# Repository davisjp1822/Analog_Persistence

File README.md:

# Analog_Persistence
Educational board showing an industrial 4-20mA or 0-10V input using a MCP3424 A/D and AD8220 Diffamp

Purchase the complete board at the [ThreeML website](https://www.three-ml.com/product/analog-persistence/)

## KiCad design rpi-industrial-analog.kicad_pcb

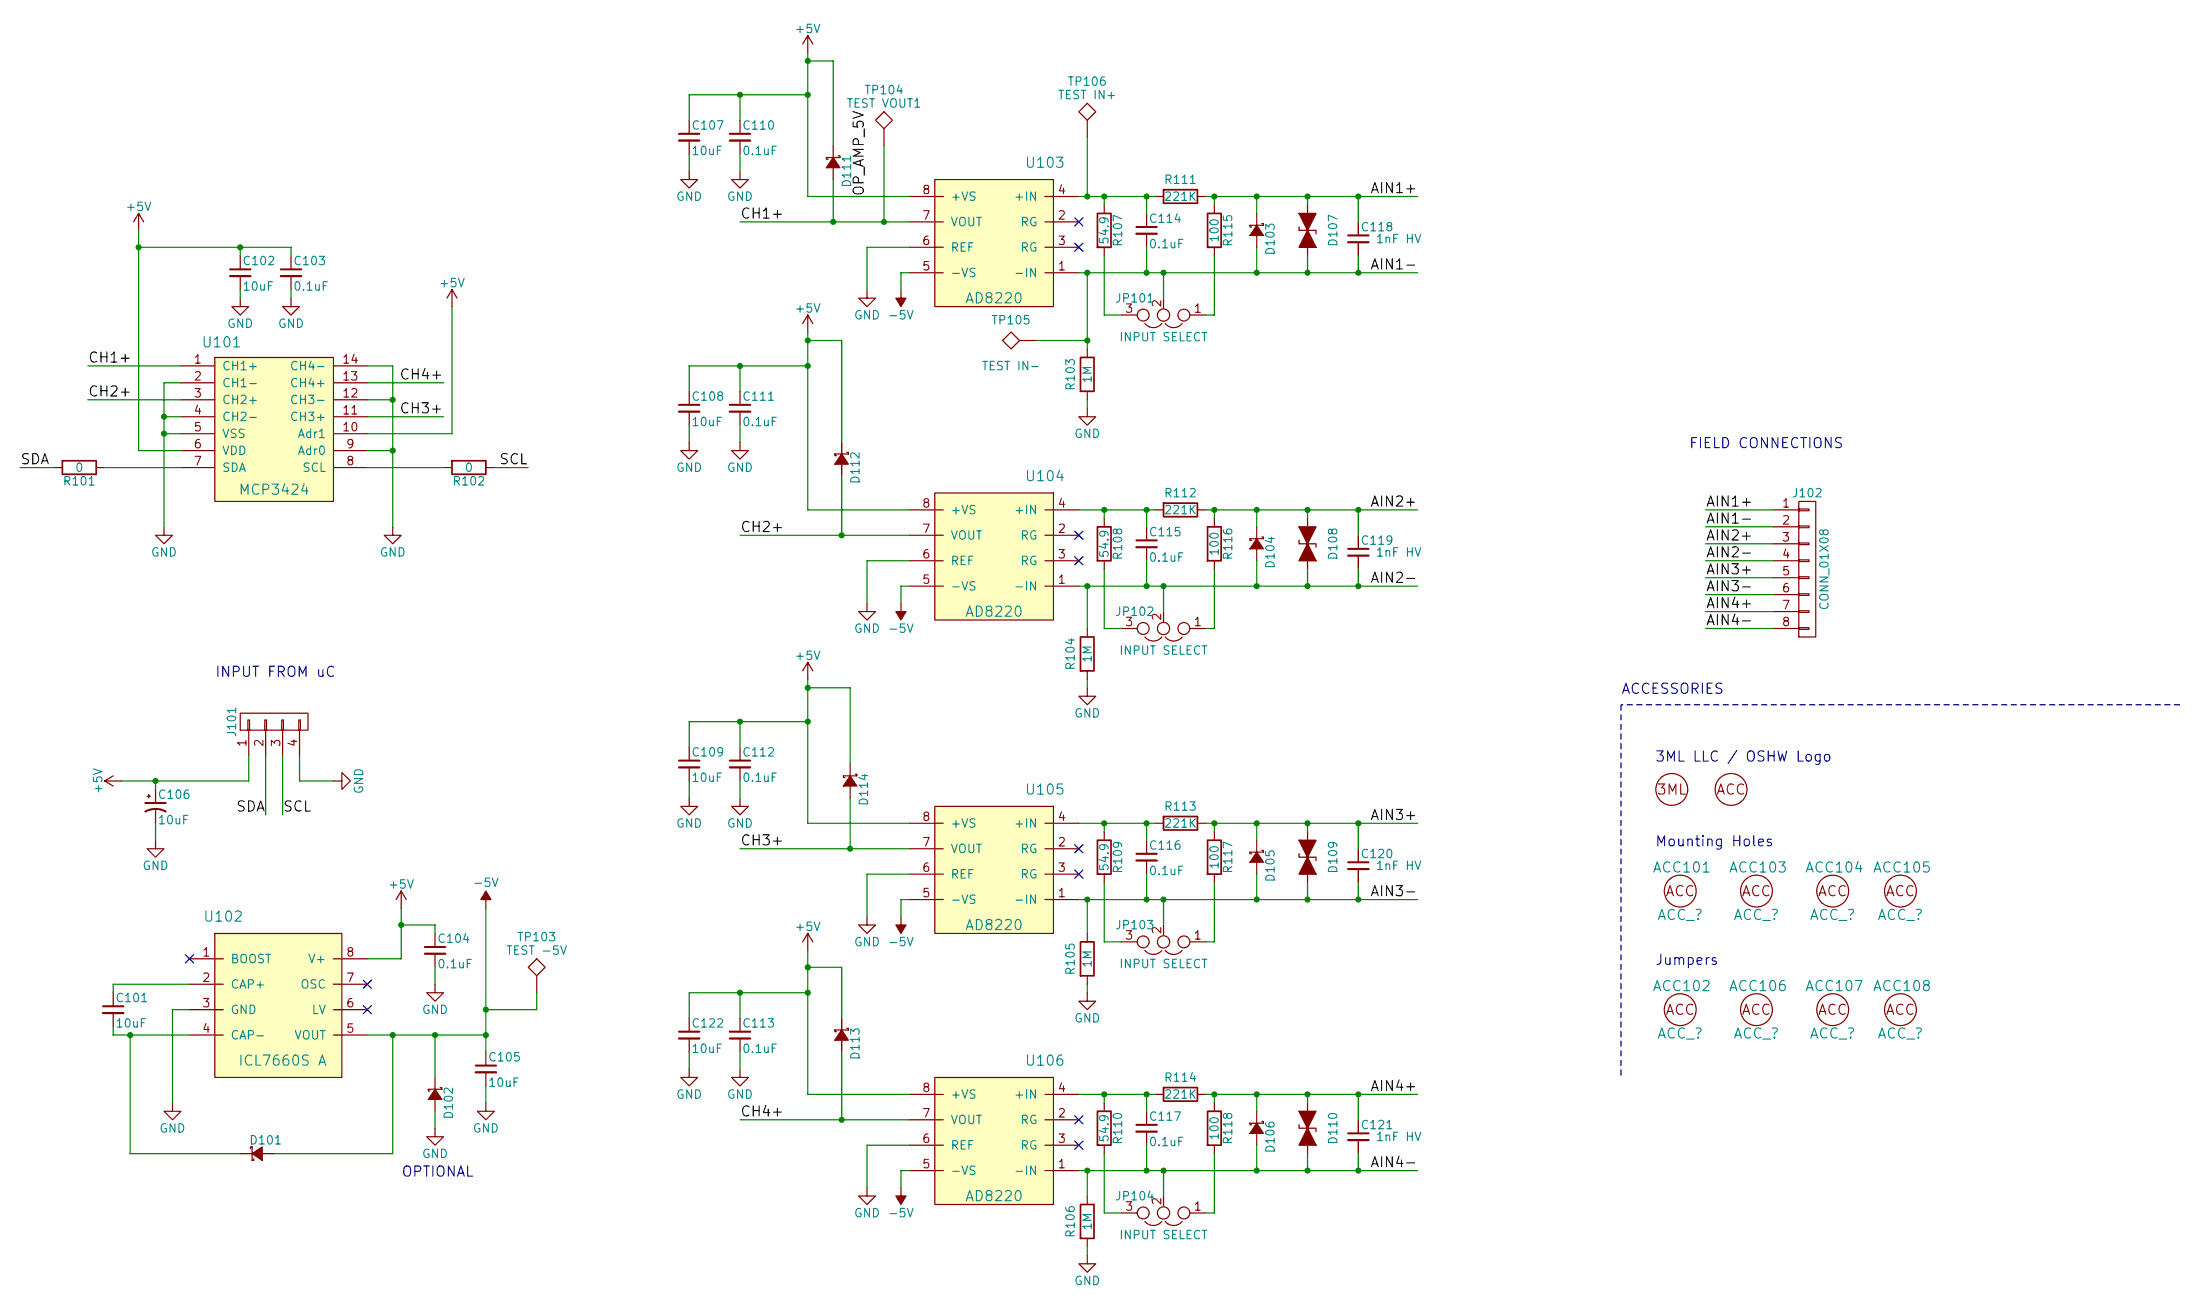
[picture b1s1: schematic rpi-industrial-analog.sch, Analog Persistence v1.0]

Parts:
ACC101, ACC103, ACC104, ACC105: ACC_?; MountingHole_3.2mm_M3_DIN965; MPN X
ACC102, ACC106, ACC107, ACC108: ACC_?; X; MPN NPB02SVAN-RC
ACC109: ACC_?; OSHW-Logo_11.4x12mm_SilkScreen
C101, C102, C105, C107, C108, C109, C122: 10uF; C_0805; MPN CL21B106KOQNNNG
C103, C104, C110, C111, C112, C113, C114, C115, C116, C117: 0.1uF; C_0805; MPN 08055C104KAT2A
C106: 10uF; CP_Tantalum_Case-A_EIA-3216-18_Reflow; MPN F931A106KAA
C118, C119, C120, C121: 1nF HV; C_0805; MPN 102R15W102KV4E
D101, D102, D103, D104, D105, D106, D111, D112, D113, D114: D_Schottky_Small_ALT; D_SOD-323; MPN NSR0530HT1GOSCT-ND
D107, D108, D109, D110: SMBJ20CA; DO-214AA_Hand_Soldering; MPN SMBJ20CALFCT-ND
J101: CONN_01X04; Pin_Header_Straight_1x04_Pitch2.54mm; MPN M20-9990445
J102: CONN_01X08; Phoenix-1x8-1935226; MPN 1935226
JP101, JP102, JP103, JP104: INPUT SELECT; Sullins-1x3-Jumper-GRPB031VWTC-RC; MPN GRPB031VWTC-RC
LG101: 3ML_LOGO; MPN X
R101, R102: 0; R_0805; MPN ValueRC0805JR-070RL
R103, R104, R105, R106: 1M; R_0805; MPN RMCF0805JT1M00
R107, R108, R109, R110: 54.9; R_0805; MPN ERA-6AEB5492V
R111, R112, R113, R114: 221K; R_0805; MPN ERA-6AEB2213V
R115, R116, R117, R118: 100; R_0805; MPN PHP00805E1000BST1
TP103: TEST -5V; Keystone_5000_Test_Point_Mini; MPN 5000
TP104: TEST VOUT1; Keystone_5000_Test_Point_Mini; MPN 5000
TP105: TEST IN-; Keystone_5000_Test_Point_Mini; MPN 5000
TP106: TEST IN+; Keystone_5000_Test_Point_Mini; MPN 5000
U101: MCP3424; SOIC-14_3.9x8.7mm_Pitch1.27mm; MPN MCP3424-E/SL
U102: ICL7660S A; SOIC-8_3.9x4.9mm_Pitch1.27mm; MPN ICL7660AIBAZA
U103, U104, U105, U106: AD8220; MSOP-8_3x3mm_Pitch0.65mm; MPN AD8220ARMZ

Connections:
+5V: C102.1, C103.1, C104.1, C106.1, C107.1, C108.1, C109.1, C110.1, C111.1, C112.1, C113.1, C122.1, D111.1 (K), D112.1 (K), D113.1 (K), D114.1 (K), J101.1, U101.6 (VDD), U101.10 (Adr1), U102.8 (V+), U103.8 (+VS), U104.8 (+VS), U105.8 (+VS), U106.8 (+VS)
-5V: C105.1, D101.2 (A), D102.1 (K), TP103.1, U102.5 (VOUT), U103.5 (-VS), U104.5 (-VS), U105.5 (-VS), U106.5 (-VS); also elsewhere on the board
/AIN1+: C118.1, D103.1 (K), D107.1 (A1), J102.1, R111.1, R115.1
/AIN1-: C114.2, C118.2, D103.2 (A), D107.2 (A2), J102.2, JP101.2, R103.1, TP105.1, U103.1 (-IN); also elsewhere on the board
/AIN2+: C119.1, D104.1 (K), D108.1 (A1), J102.3, R112.1, R116.1
/AIN2-: C115.2, C119.2, D104.2 (A), D108.2 (A2), J102.4, JP102.2, R104.1, U104.1 (-IN)
/AIN3+: C120.1, D105.1 (K), D109.1 (A1), J102.5, R113.1, R117.1
/AIN3-: C116.2, C120.2, D105.2 (A), D109.2 (A2), J102.6, JP103.2, R105.1, U105.1 (-IN)
/AIN4+: C121.1, D106.1 (K), D110.1 (A1), J102.7, R114.1, R118.1
/AIN4-: C117.2, C121.2, D106.2 (A), D110.2 (A2), J102.8, JP104.2, R106.1, U106.1 (-IN)
/CH1+: D111.2 (A), TP104.1, U101.1 (CH1+), U103.7 (VOUT); also elsewhere on the board
/CH2+: D112.2 (A), U101.3 (CH2+), U104.7 (VOUT)
/CH3+: D114.2 (A), U101.11 (CH3+), U105.7 (VOUT)
/CH4+: D113.2 (A), U101.13 (CH4+), U106.7 (VOUT)
/SCL: J101.3, R102.1
/SDA: J101.2, R101.2
GND: C102.2, C103.2, C104.2, C105.2, C106.2, C107.2, C108.2, C109.2, C110.2, C111.2, C112.2, C113.2, C122.2, D102.2 (A), J101.4, R103.2, R104.2, R105.2, R106.2, U101.2 (CH1-), U101.4 (CH2-), U101.5 (VSS), U101.9 (Adr0), U101.12 (CH3-), U101.14 (CH4-), U102.3 (GND), U103.6 (REF), U104.6 (REF), U105.6 (REF), U106.6 (REF)
unnamed: C101.1, U102.2 (CAP+)
unnamed: C101.2, D101.1 (K), U102.4 (CAP-)
unnamed 19: C114.1, R107.1, R111.2, TP106.1, U103.4 (+IN); also elsewhere on the board
unnamed: C115.1, R108.1, R112.2, U104.4 (+IN)
unnamed: C116.1, R109.1, R113.2, U105.4 (+IN)
unnamed: C117.1, R110.1, R114.2, U106.4 (+IN)
unnamed: JP101.1, R115.2
unnamed: JP101.3, R107.2
unnamed: JP102.1, R116.2
unnamed: JP102.3, R108.2
unnamed: JP103.1, R117.2
unnamed: JP103.3, R109.2
unnamed: JP104.1, R118.2
unnamed: JP104.3, R110.2
unnamed: R101.1, U101.7 (SDA)
unnamed: R102.2, U101.8 (SCL)

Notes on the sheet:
INPUT FROM uC
FIELD CONNECTIONS
OPTIONAL
3ML LLC / OSHW Logo
ACCESSORIES
Mounting Holes
Jumpers

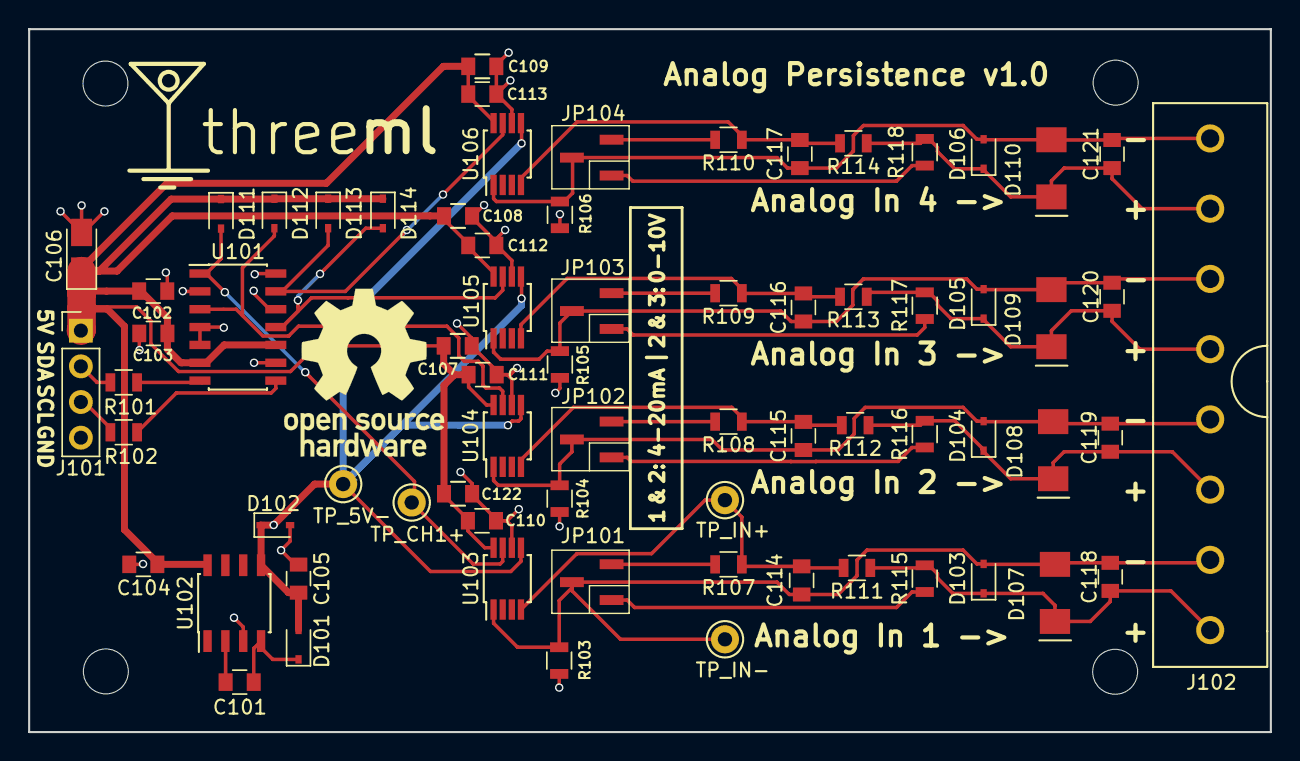
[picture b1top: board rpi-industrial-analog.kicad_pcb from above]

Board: 2 copper layers, 88.4 x 50.0 mm, 76 parts (0 on the bottom side), 33 nets.

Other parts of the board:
TP_5V-: TEST -5V; Keystone_5000_Test_Point_Mini
TP_CH1+: TEST VOUT1; Keystone_5000_Test_Point_Mini
TP_IN+: TEST IN+; Keystone_5000_Test_Point_Mini
TP_IN-: TEST IN-; Keystone_5000_Test_Point_Mini

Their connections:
-5V: TP_5V-.1; also elsewhere on the board
/AIN1-: TP_IN-.1; also elsewhere on the board
/CH1+: TP_CH1+.1; also elsewhere on the board
unnamed 19: TP_IN+.1; also elsewhere on the board

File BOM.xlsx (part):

Reference | Value | Characteristics | Description | MFN | Package ID | Source | Critical | Notes | Populate | MPN | Library | Library Ref
C101 | 10uF | X | 10ÂµF Â±10% 16V Ceramic Capacitor X7R 0805 (2012 Metric) | Samsung Electro-Mechanics America Inc. | 805 | Digikey | Y | X |  | CL21B106KOQNNNG | device | C_Small
C102 | 10uF | X | 10ÂµF Â±10% 16V Ceramic Capacitor X7R 0805 (2012 Metric) | Samsung Electro-Mechanics America Inc. | 805 | Digikey | Y | X |  | CL21B106KOQNNNG | device | C_Small
C103 | 0.1uF | 0.1uF 0805 capacitor | 0.10ÂµF 50V Ceramic Capacitor X7R 0805 | AVX Corporation | 805 | Digikey | Y | X |  | 08055C104KAT2A | device | C_Small
C104 | 0.1uF | 0.1uF 0805 capacitor | 0.10ÂµF 50V Ceramic Capacitor X7R 0805 | AVX Corporation | 805 | Digikey | Y | X |  | 08055C104KAT2A | device | C_Small
C105 | 10uF | X | 10ÂµF Â±10% 16V Ceramic Capacitor X7R 0805 (2012 Metric) | Samsung Electro-Mechanics America Inc. | 805 | Digikey | Y | X |  | CL21B106KOQNNNG | device | C_Small
C106 | 10uF | X | F931A106KAA | AVX Corporation | 1206 (3216 Metric) | Digikey | Y | X | 1 |  | device | CP1_Small
C107 | 10uF | X | 10ÂµF Â±10% 16V Ceramic Capacitor X7R 0805 (2012 Metric) | Samsung Electro-Mechanics America Inc. | 805 | Digikey | Y | X |  | CL21B106KOQNNNG | device | C_Small
C108 | 10uF | X | 10ÂµF Â±10% 16V Ceramic Capacitor X7R 0805 (2012 Metric) | Samsung Electro-Mechanics America Inc. | 805 | Digikey | Y | X |  | CL21B106KOQNNNG | device | C_Small
C109 | 10uF | X | 10ÂµF Â±10% 16V Ceramic Capacitor X7R 0805 (2012 Metric) | Samsung Electro-Mechanics America Inc. | 805 | Digikey | Y | X |  | CL21B106KOQNNNG | device | C_Small
C110 | 0.1uF | 0.1uF 0805 capacitor | 0.10ÂµF 50V Ceramic Capacitor X7R 0805 | AVX Corporation | 805 | Digikey | Y | X |  | 08055C104KAT2A | device | C_Small
C111 | 0.1uF | 0.1uF 0805 capacitor | 0.10ÂµF 50V Ceramic Capacitor X7R 0805 | AVX Corporation | 805 | Digikey | Y | X |  | 08055C104KAT2A | device | C_Small
C112 | 0.1uF | 0.1uF 0805 capacitor | 0.10ÂµF 50V Ceramic Capacitor X7R 0805 | AVX Corporation | 805 | Digikey | Y | X |  | 08055C104KAT2A | device | C_Small
C113 | 0.1uF | 0.1uF 0805 capacitor | 0.10ÂµF 50V Ceramic Capacitor X7R 0805 | AVX Corporation | 805 | Digikey | Y | X |  | 08055C104KAT2A | device | C_Small
C114 | 0.1uF | 0.1uF 0805 capacitor | 0.10ÂµF 50V Ceramic Capacitor X7R 0805 | AVX Corporation | 805 | Digikey | Y | X |  | 08055C104KAT2A | device | C_Small
C115 | 0.1uF | 0.1uF 0805 capacitor | 0.10ÂµF 50V Ceramic Capacitor X7R 0805 | AVX Corporation | 805 | Digikey | Y | X |  | 08055C104KAT2A | device | C_Small
C116 | 0.1uF | 0.1uF 0805 capacitor | 0.10ÂµF 50V Ceramic Capacitor X7R 0805 | AVX Corporation | 805 | Digikey | Y | X |  | 08055C104KAT2A | device | C_Small
C117 | 0.1uF | 0.1uF 0805 capacitor | 0.10ÂµF 50V Ceramic Capacitor X7R 0805 | AVX Corporation | 805 | Digikey | Y | X |  | 08055C104KAT2A | device | C_Small
C118 | 1nF HV | X | CAP CER 1000PF 1KV X7R 0805 | Johanson Dielectrics Inc. | 805 | Digikey | Y | X | 1 | 102R15W102KV4E | device | C_Small
C119 | 1nF HV | X | CAP CER 1000PF 1KV X7R 0805 | Johanson Dielectrics Inc. | 805 | Digikey | Y | X | 1 | 102R15W102KV4E | device | C_Small
C120 | 1nF HV | X | CAP CER 1000PF 1KV X7R 0805 | Johanson Dielectrics Inc. | 805 | Digikey | Y | X | 1 | 102R15W102KV4E | device | C_Small
C121 | 1nF HV | X | CAP CER 1000PF 1KV X7R 0805 | Johanson Dielectrics Inc. | 805 | Digikey | Y | X | 1 | 102R15W102KV4E | device | C_Small
C122 | 10uF | X | 10ÂµF Â±10% 16V Ceramic Capacitor X7R 0805 (2012 Metric) | Samsung Electro-Mechanics America Inc. | 805 | Digikey | Y | X |  | CL21B106KOQNNNG | device | C_Small
D101 | D_Schottky_Small_ALT | X | Diode Schottky 30V 500mA (DC) Surface Mount SOD-323 | ON Semiconductor | SOD-323 | Digikey | Y | X |  | NSR0530HT1GOSCT-ND | device | D_Schottky_Small_ALT
D102 | D_Schottky_Small_ALT | X | Diode Schottky 30V 500mA (DC) Surface Mount SOD-323 | ON Semiconductor | SOD-323 | Digikey | Y | X |  | NSR0530HT1GOSCT-ND | device | D_Schottky_Small_ALT
D103 | D_Schottky_Small_ALT | X | Diode Schottky 30V 500mA (DC) Surface Mount SOD-323 | ON Semiconductor | SOD-323 | Digikey | Y | X |  | NSR0530HT1GOSCT-ND | device | D_Schottky_Small_ALT
D104 | D_Schottky_Small_ALT | X | Diode Schottky 30V 500mA (DC) Surface Mount SOD-323 | ON Semiconductor | SOD-323 | Digikey | Y | X |  | NSR0530HT1GOSCT-ND | device | D_Schottky_Small_ALT
D105 | D_Schottky_Small_ALT | X | Diode Schottky 30V 500mA (DC) Surface Mount SOD-323 | ON Semiconductor | SOD-323 | Digikey | Y | X |  | NSR0530HT1GOSCT-ND | device | D_Schottky_Small_ALT
D106 | D_Schottky_Small_ALT | X | Diode Schottky 30V 500mA (DC) Surface Mount SOD-323 | ON Semiconductor | SOD-323 | Digikey | Y | X |  | NSR0530HT1GOSCT-ND | device | D_Schottky_Small_ALT
D107 | SMBJ20CA | X | TVS Diode | Littelfuse Inc | DO-214AA | Digikey | Y | X |  | SMBJ20CALFCT-ND | 3ML_LLC_Component_Library | TVS_Small
D108 | SMBJ20CA | X | TVS Diode | Littelfuse Inc | DO-214AA | Digikey | Y | X |  | SMBJ20CALFCT-ND | 3ML_LLC_Component_Library | TVS_Small
D109 | SMBJ20CA | X | TVS Diode | Littelfuse Inc | DO-214AA | Digikey | Y | X |  | SMBJ20CALFCT-ND | 3ML_LLC_Component_Library | TVS_Small
D110 | SMBJ20CA | X | TVS Diode | Littelfuse Inc | DO-214AA | Digikey | Y | X |  | SMBJ20CALFCT-ND | 3ML_LLC_Component_Library | TVS_Small
D111 | D_Schottky_Small_ALT | X | Diode Schottky 30V 500mA (DC) Surface Mount SOD-323 | ON Semiconductor | SOD-323 | Digikey | Y | X |  | NSR0530HT1GOSCT-ND | device | D_Schottky_Small_ALT
D112 | D_Schottky_Small_ALT | X | Diode Schottky 30V 500mA (DC) Surface Mount SOD-323 | ON Semiconductor | SOD-323 | Digikey | Y | X |  | NSR0530HT1GOSCT-ND | device | D_Schottky_Small_ALT
D113 | D_Schottky_Small_ALT | X | Diode Schottky 30V 500mA (DC) Surface Mount SOD-323 | ON Semiconductor | SOD-323 | Digikey | Y | X |  | NSR0530HT1GOSCT-ND | device | D_Schottky_Small_ALT
D114 | D_Schottky_Small_ALT | X | Diode Schottky 30V 500mA (DC) Surface Mount SOD-323 | ON Semiconductor | SOD-323 | Digikey | Y | X |  | NSR0530HT1GOSCT-ND | device | D_Schottky_Small_ALT
J101 | CONN_01X04 | X | 1x4 0.100 PITCH PIN HEADER | Harwin | TH | Digikey | Y | X | 1 | M20-9990445 | conn | CONN_01X04
J102 | CONN_01X08 | X | 8 Position Wire to Board Terminal Block Horizontal with Board 0.197" (5.00mm) T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 | Phoenix Contact | TH | Digikey | Y | X |  | 1935226 | conn | CONN_01X08
JP101 | INPUT SELECT | X | 3 Positions Header Unshrouded Connector 0.050" (1.27mm) Surface Mount Gold | Sullins Connector Solutions | X | Digikey | Y | X |  | GRPB031VWTC-RC | device | Jumper_NC_Dual
JP102 | INPUT SELECT | X | 3 Positions Header Unshrouded Connector 0.050" (1.27mm) Surface Mount Gold | Sullins Connector Solutions | X | Digikey | Y | X |  | GRPB031VWTC-RC | device | Jumper_NC_Dual
JP103 | INPUT SELECT | X | 3 Positions Header Unshrouded Connector 0.050" (1.27mm) Surface Mount Gold | Sullins Connector Solutions | X | Digikey | Y | X |  | GRPB031VWTC-RC | device | Jumper_NC_Dual
JP104 | INPUT SELECT | X | 3 Positions Header Unshrouded Connector 0.050" (1.27mm) Surface Mount Gold | Sullins Connector Solutions | X | Digikey | Y | X |  | GRPB031VWTC-RC | device | Jumper_NC_Dual
R101 | 0 | X | RES SMD 0.0 OHM JUMPER 1/8W 0805 | Yageo | 805 | Digikey | Y | X |  | RC0805JR-070RL | device | R
R102 | 0 | X | RES SMD 0.0 OHM JUMPER 1/8W 0805 | Yageo | 805 | Digikey | Y | X |  | RC0805JR-070RL | device | R
R103 | 1M | X | RES SMD 1M OHM 5% 1/8W 0805 | Stackpole Electronics Inc. | 805 | Digikey | Y | X | 1 | RMCF0805JT1M00 | device | R
R104 | 1M | X | RES SMD 1M OHM 5% 1/8W 0805 | Stackpole Electronics Inc. | 805 | Digikey | Y | X | 1 | RMCF0805JT1M00 | device | R
R105 | 1M | X | RES SMD 1M OHM 5% 1/8W 0805 | Stackpole Electronics Inc. | 805 | Digikey | Y | X | 1 | RMCF0805JT1M00 | device | R
R106 | 1M | X | RES SMD 1M OHM 5% 1/8W 0805 | Stackpole Electronics Inc. | 805 | Digikey | Y | X | 1 | RMCF0805JT1M00 | device | R
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
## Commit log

2017-03-27 First Commit
    Adding files, getting ready to start board layout
2017-03-28 Layout complete
2017-03-28 adding logos and mounting holes
2017-03-29 fixing some routing errors
2017-03-29 fixing some silk screen issues
2017-03-29 added 3d file for phoenix connector
2017-08-01 revised board for production and added 1M caps so that this thing works
2017-08-02 adding gerbers, fixing DRC, adding overvoltage diodes to MCP inputs
2017-08-07 cleaning-up Gerbers and step 1 of migrating footprints to master 3ML library
2017-08-07 adding master footprint library as submodule
2017-08-07 schematic library switched to master library
2017-08-07 updating footprints to use master library
2017-09-05 kicad version bump updating files
2017-09-16 Create LICENSE
2018-06-11 updating sub-repo
2018-06-11 updating kicad version
2018-06-11 adding RPi Example Code

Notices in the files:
rpi-industrial-analog.sch:
Licensed under the GPL v3
